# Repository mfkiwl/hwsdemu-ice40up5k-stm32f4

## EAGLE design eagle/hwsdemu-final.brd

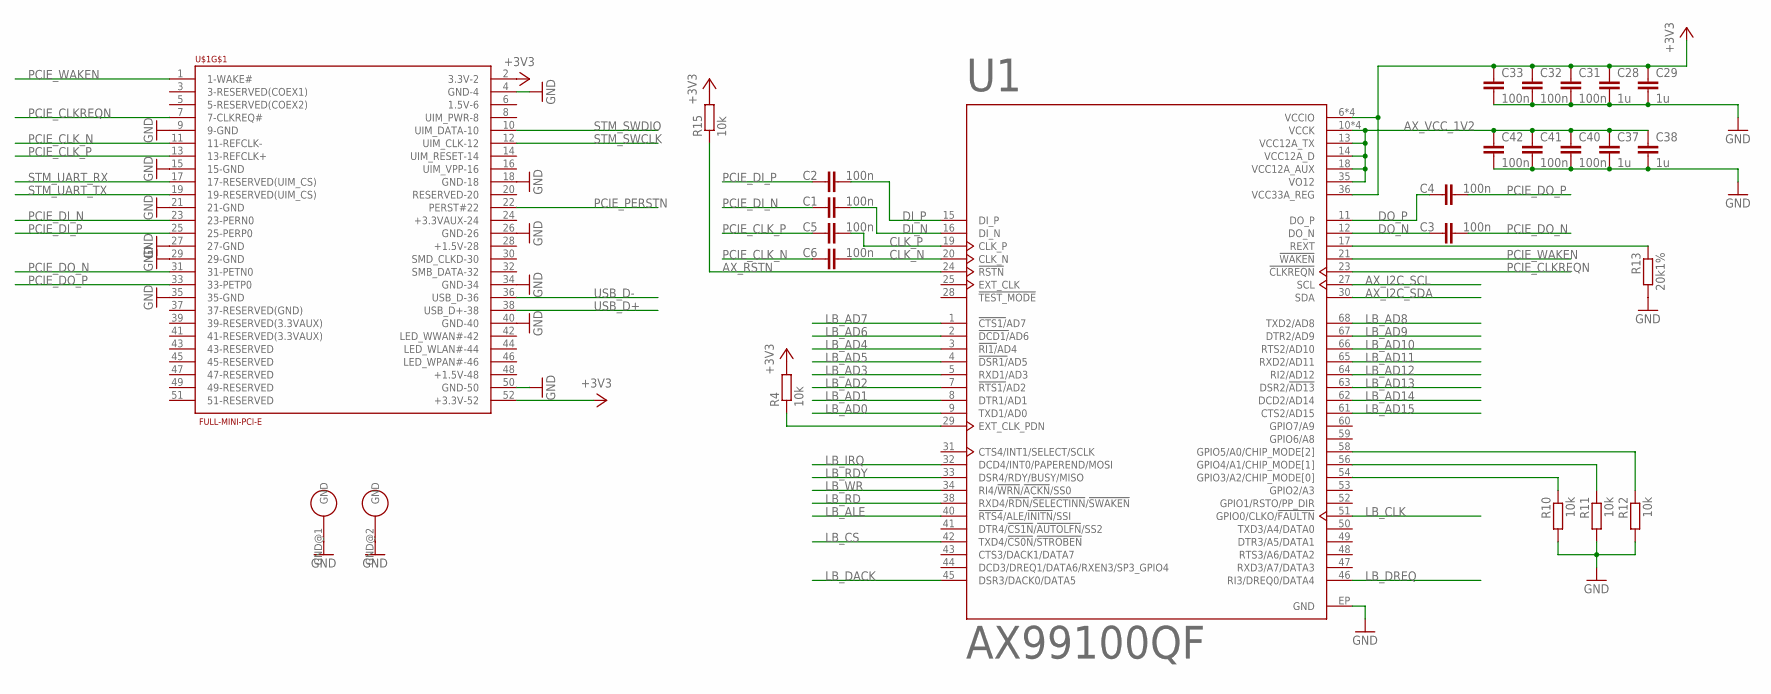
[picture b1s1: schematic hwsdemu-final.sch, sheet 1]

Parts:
C1, C2, C3, C4, C5, C6, C31, C32, C33, C40, C41, C42: 100n; C0402
C28, C29, C37, C38: 1u; C0402
R4, R10, R11, R12, R15: 10k; R0402
R13: 20k1%; R0402
U1: AX99100QF; QFN40P800X800X90-69N
U$1: FULL-MINI-PCI-E

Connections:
+3V3: C28.1, C29.1, C31.1, C32.1, C33.1, R4.2, R15.2, U1.6 (VCCIO), U1.26 (VCCIO), U1.36 (VCC33A_REG), U1.39 (VCCIO), U1.55 (VCCIO), U$1.2 (3.3V-2), U$1.52 (+3.3V-52); also elsewhere on the board
AX_I2C_SCL: U1.27 (SCL); also elsewhere on the board
AX_I2C_SDA: U1.30 (SDA); also elsewhere on the board
AX_RSTN: R15.1, U1.24 (!RSTN); also elsewhere on the board
AX_VCC_1V2: C37.1, C38.1, C40.1, C41.1, C42.1, U1.10 (VCCK), U1.13 (VCC12A_TX), U1.14 (VCC12A_D), U1.18 (VCC12A_AUX), U1.22 (VCCK), U1.35 (VO12), U1.37 (VCCK), U1.57 (VCCK)
CLK_N: C6.2, U1.20 (CLK_N)
CLK_P: C5.2, U1.19 (CLK_P)
DI_N: C1.2, U1.16 (DI_N)
DI_P: C2.2, U1.15 (DI_P)
DO_N: C3.1, U1.12 (DO_N)
DO_P: C4.1, U1.11 (DO_P)
GND: C28.2, C29.2, C31.2, C32.2, C33.2, C37.2, C38.2, C40.2, C41.2, C42.2, R10.2, R11.2, R12.2, R13.2, U1.EP (GND), U$1.4 (GND-4), U$1.9 (9-GND), U$1.15 (15-GND), U$1.18 (GND-18), U$1.21 (21-GND), U$1.26 (GND-26), U$1.27 (27-GND), U$1.29 (29-GND), U$1.34 (GND-34), U$1.35 (35-GND), U$1.40 (GND-40), U$1.50 (GND-50), U$1.GND@1 (GND), U$1.GND@2 (GND); also elsewhere on the board
LB_AD0: U1.9 (TXD1/AD0); also elsewhere on the board
LB_AD1: U1.8 (DTR1/AD1); also elsewhere on the board
LB_AD2: U1.7 (!RTS1/!AD2); also elsewhere on the board
LB_AD3: U1.5 (RXD1/AD3); also elsewhere on the board
LB_AD4: U1.3 (!RI1/!AD4); also elsewhere on the board
LB_AD5: U1.4 (!DSR1/!AD5); also elsewhere on the board
LB_AD6: U1.2 (!DCD1/!AD6); also elsewhere on the board
LB_AD7: U1.1 (!CTS1/!AD7); also elsewhere on the board
LB_AD8: U1.68 (TXD2/AD8); also elsewhere on the board
LB_AD9: U1.67 (DTR2/AD9); also elsewhere on the board
LB_AD10: U1.66 (RTS2/AD10); also elsewhere on the board
LB_AD11: U1.65 (RXD2/AD11); also elsewhere on the board
LB_AD12: U1.64 (RI2/AD12); also elsewhere on the board
LB_AD13: U1.63 (DSR2/!AD13); also elsewhere on the board
LB_AD14: U1.62 (DCD2/AD14); also elsewhere on the board
LB_AD15: U1.61 (CTS2/AD15); also elsewhere on the board
LB_ALE: U1.40 (!RTS4!/ALE/!INITN!/SSI); also elsewhere on the board
LB_CLK: U1.51 (GPIO0/CLKO/!FAULTN); also elsewhere on the board
LB_CS: U1.42 (TXD4/!CS0N!/!STROBEN); also elsewhere on the board
LB_DACK: U1.45 (DSR3/DACK0/DATA5); also elsewhere on the board
LB_DREQ: U1.46 (RI3/DREQ0/DATA4); also elsewhere on the board
LB_IRQ: U1.32 (DCD4/INT0/PAPEREND/MOSI); also elsewhere on the board
LB_RD: U1.38 (RXD4/!RDN!/!SELECTINN!/!SWAKEN); also elsewhere on the board
LB_RDY: U1.33 (DSR4/RDY/BUSY/MISO); also elsewhere on the board
LB_WR: U1.34 (RI4/!WRN!/!ACKN!/SS0); also elsewhere on the board
unnamed: R4.1, U1.29 (EXT_CLK_PDN)
unnamed: R10.1, U1.54 (GPIO3/A2/CHIP_MODE[0])
unnamed: R11.1, U1.56 (GPIO4/A1/CHIP_MODE[1])
unnamed: R12.1, U1.58 (GPIO5/A0/CHIP_MODE[2])
unnamed: R13.1, U1.17 (REXT)
PCIE_CLKREQN: U1.23 (!CLKREQN), U$1.7 (7-CLKREQ#)
PCIE_CLK_N: C6.1, U$1.11 (11-REFCLK-)
PCIE_CLK_P: C5.1, U$1.13 (13-REFCLK+)
PCIE_DI_N: C1.1, U$1.23 (23-PERN0)
PCIE_DI_P: C2.1, U$1.25 (25-PERP0)
PCIE_DO_N: C3.2, U$1.31 (31-PETN0)
PCIE_DO_P: C4.2, U$1.33 (33-PETP0)
PCIE_PERSTN: U$1.22 (PERST#22); also elsewhere on the board
PCIE_WAKEN: U1.21 (!WAKEN), U$1.1 (1-WAKE#)
STM_SWCLK: U$1.12 (UIM_CLK-12); also elsewhere on the board
STM_SWDIO: U$1.10 (UIM_DATA-10); also elsewhere on the board
STM_UART_RX: U$1.17 (17-RESERVED(UIM_CS)); also elsewhere on the board
STM_UART_TX: U$1.19 (19-RESERVED(UIM_CS)); also elsewhere on the board
USB_D+: U$1.38 (USB_D+-38); also elsewhere on the board
USB_D-: U$1.36 (USB_D-36); also elsewhere on the board

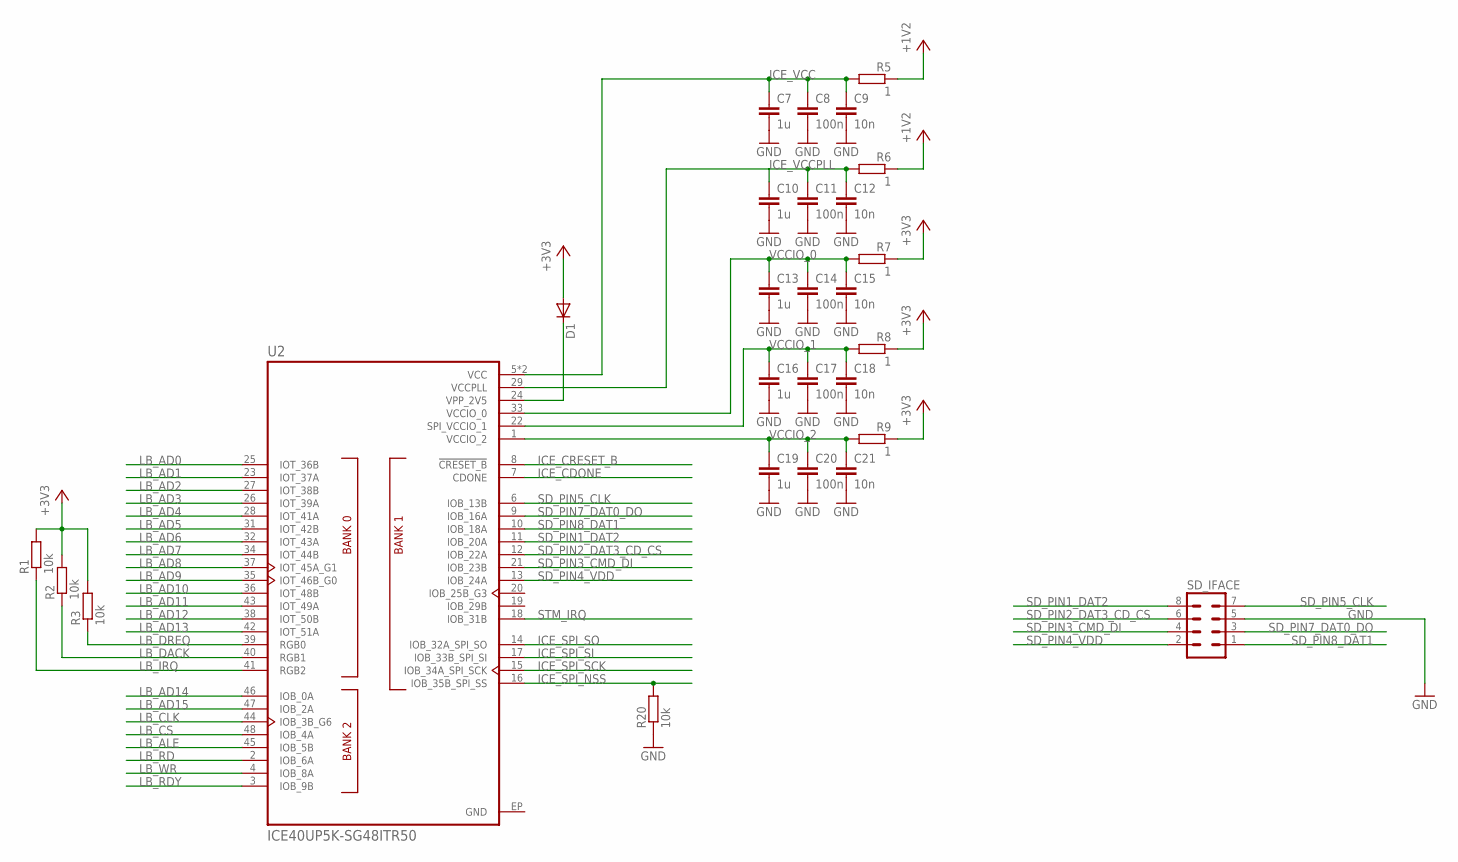
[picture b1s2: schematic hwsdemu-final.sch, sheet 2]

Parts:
C7, C10, C13, C16, C19: 1u; C0402
C8, C11, C14, C17, C20: 100n; C0402
C9, C12, C15, C18, C21: 10n; C0402
D1: DIODE-MICROMELF-W; MICROMELF-W
R1, R2, R3, R20: 10k; R0402
R5, R6, R7, R8, R9: 1; R0402
SD_IFACE: MA04-2
U2: ICE40UP5K-SG48ITR50; QFN50P700X700X100-49N

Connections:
+1V2: R5.1, R6.1; also elsewhere on the board
+3V3: D1.A, R1.2, R2.2, R3.2, R7.1, R8.1, R9.1; also elsewhere on the board
GND: C7.2, C8.2, C9.2, C10.2, C11.2, C12.2, C13.2, C14.2, C15.2, C16.2, C17.2, C18.2, C19.2, C20.2, C21.2, R20.1, SD_IFACE.5, U2.EP (GND); also elsewhere on the board
ICE_CDONE: U2.7 (CDONE); also elsewhere on the board
ICE_CRESET_B: U2.8 (!CRESET_B); also elsewhere on the board
ICE_SPI_NSS: R20.2, U2.16 (IOB_35B_SPI_SS); also elsewhere on the board
ICE_SPI_SCK: U2.15 (IOB_34A_SPI_SCK); also elsewhere on the board
ICE_SPI_SI: U2.17 (IOB_33B_SPI_SI); also elsewhere on the board
ICE_SPI_SO: U2.14 (IOB_32A_SPI_SO); also elsewhere on the board
ICE_VCC: C7.1, C8.1, C9.1, R5.2, U2.5 (VCC), U2.30 (VCC)
ICE_VCCPLL: C10.1, C11.1, C12.1, R6.2, U2.29 (VCCPLL)
LB_AD0: U2.25 (IOT_36B); also elsewhere on the board
LB_AD1: U2.23 (IOT_37A); also elsewhere on the board
LB_AD2: U2.27 (IOT_38B); also elsewhere on the board
LB_AD3: U2.26 (IOT_39A); also elsewhere on the board
LB_AD4: U2.28 (IOT_41A); also elsewhere on the board
LB_AD5: U2.31 (IOT_42B); also elsewhere on the board
LB_AD6: U2.32 (IOT_43A); also elsewhere on the board
LB_AD7: U2.34 (IOT_44B); also elsewhere on the board
LB_AD8: U2.37 (IOT_45A_G1); also elsewhere on the board
LB_AD9: U2.35 (IOT_46B_G0); also elsewhere on the board
LB_AD10: U2.36 (IOT_48B); also elsewhere on the board
LB_AD11: U2.43 (IOT_49A); also elsewhere on the board
LB_AD12: U2.38 (IOT_50B); also elsewhere on the board
LB_AD13: U2.42 (IOT_51A); also elsewhere on the board
LB_AD14: U2.46 (IOB_0A); also elsewhere on the board
LB_AD15: U2.47 (IOB_2A); also elsewhere on the board
LB_ALE: U2.45 (IOB_5B); also elsewhere on the board
LB_CLK: U2.44 (IOB_3B_G6); also elsewhere on the board
LB_CS: U2.48 (IOB_4A); also elsewhere on the board
LB_DACK: R2.1, U2.40 (RGB1); also elsewhere on the board
LB_DREQ: R3.1, U2.39 (RGB0); also elsewhere on the board
LB_IRQ: R1.1, U2.41 (RGB2); also elsewhere on the board
LB_RD: U2.2 (IOB_6A); also elsewhere on the board
LB_RDY: U2.3 (IOB_9B); also elsewhere on the board
LB_WR: U2.4 (IOB_8A); also elsewhere on the board
unnamed: D1.C, U2.24 (VPP_2V5)
SD_PIN1_DAT2: SD_IFACE.8, U2.11 (IOB_20A)
SD_PIN2_DAT3_CD_CS: SD_IFACE.6, U2.12 (IOB_22A)
SD_PIN3_CMD_DI: SD_IFACE.4, U2.21 (IOB_23B)
SD_PIN4_VDD: SD_IFACE.2, U2.13 (IOB_24A)
SD_PIN5_CLK: SD_IFACE.7, U2.6 (IOB_13B)
SD_PIN7_DAT0_DO: SD_IFACE.3, U2.9 (IOB_16A)
SD_PIN8_DAT1: SD_IFACE.1, U2.10 (IOB_18A)
STM_IRQ: U2.18 (IOB_31B); also elsewhere on the board
VCCIO_0: C13.1, C14.1, C15.1, R7.2, U2.33 (VCCIO_0)
VCCIO_1: C16.1, C17.1, C18.1, R8.2, U2.22 (SPI_VCCIO_1)
VCCIO_2: C19.1, C20.1, C21.1, R9.2, U2.1 (VCCIO_2)

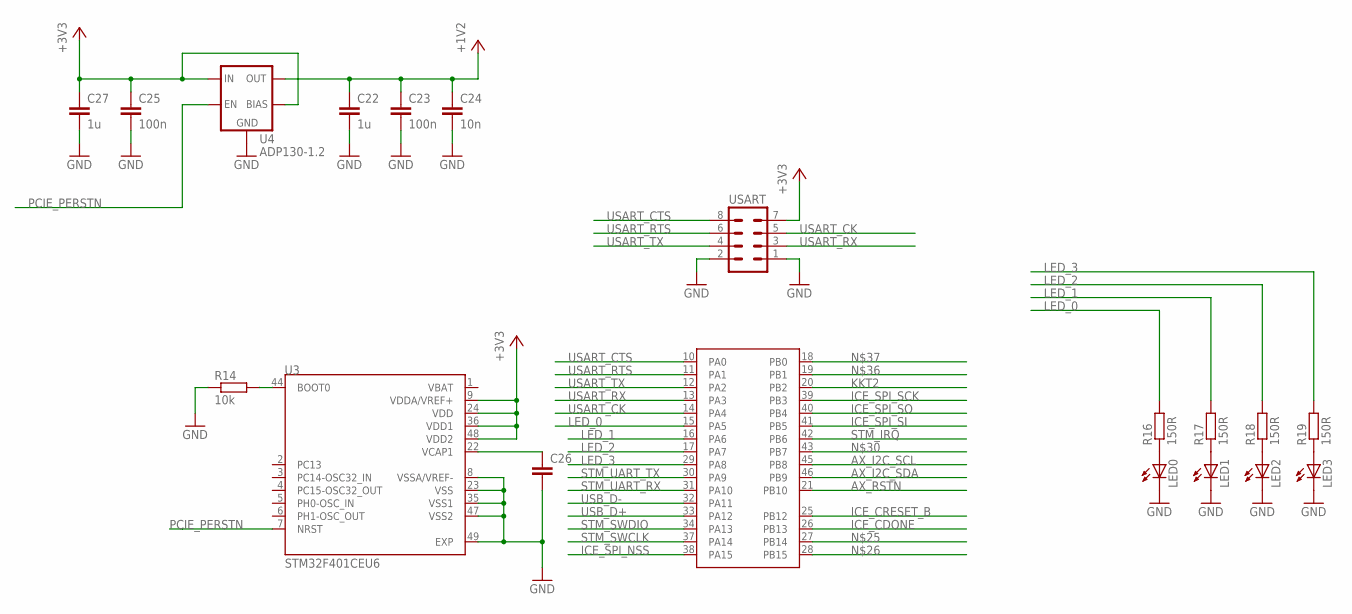
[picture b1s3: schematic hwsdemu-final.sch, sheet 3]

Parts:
C22, C27: 1u; C0402
C23, C25: 100n; C0402
C24: 10n; C0402
C26: C-EUC0402; C0402
LED0, LED1, LED2, LED3: LEDCHIP-LED0603; CHIP-LED0603
R14: 10k; R0402
R16, R17, R18, R19: 150R; R0402
U3: STM32F401CEU6; QFN50P700X700X60-49N
U4: ADP130-1.2; SOT23-5
USART: MA04-2

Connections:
+1V2: C22.1, C23.1, C24.1, U4.5 (OUT); also elsewhere on the board
+3V3: C25.1, C27.1, U3.9 (VDDA/VREF+), U3.24 (VDD), U3.36 (VDD1), U3.48 (VDD2), U4.1 (IN), U4.4 (BIAS), USART.7; also elsewhere on the board
AX_I2C_SCL: U3.45 (PB8); also elsewhere on the board
AX_I2C_SDA: U3.46 (PB9); also elsewhere on the board
AX_RSTN: U3.21 (PB10); also elsewhere on the board
GND: C22.2, C23.2, C24.2, C25.2, C26.2, C27.2, LED0.C, LED1.C, LED2.C, LED3.C, R14.1, U3.8 (VSSA/VREF-), U3.23 (VSS), U3.35 (VSS1), U3.47 (VSS2), U3.49 (EXP), U4.2 (GND), USART.1, USART.2; also elsewhere on the board
ICE_CDONE: U3.26 (PB13); also elsewhere on the board
ICE_CRESET_B: U3.25 (PB12); also elsewhere on the board
ICE_SPI_NSS: U3.38 (PA15); also elsewhere on the board
ICE_SPI_SCK: U3.39 (PB3); also elsewhere on the board
ICE_SPI_SI: U3.41 (PB5); also elsewhere on the board
ICE_SPI_SO: U3.40 (PB4); also elsewhere on the board
KKT2: U3.20 (PB2)
LED_0: R16.2, U3.15 (PA5)
LED_1: R17.2, U3.16 (PA6)
LED_2: R18.2, U3.17 (PA7)
LED_3: R19.2, U3.29 (PA8)
unnamed: R14.2, U3.44 (BOOT0)
unnamed: C26.1, U3.22 (VCAP1)
unnamed: LED0.A, R16.1
unnamed: LED1.A, R17.1
unnamed: LED2.A, R18.1
unnamed: LED3.A, R19.1
PCIE_PERSTN: U3.7 (NRST), U4.3 (EN); also elsewhere on the board
STM_IRQ: U3.42 (PB6); also elsewhere on the board
STM_SWCLK: U3.37 (PA14); also elsewhere on the board
STM_SWDIO: U3.34 (PA13); also elsewhere on the board
STM_UART_RX: U3.31 (PA10); also elsewhere on the board
STM_UART_TX: U3.30 (PA9); also elsewhere on the board
USART_CK: U3.14 (PA4), USART.5
USART_CTS: U3.10 (PA0), USART.8
USART_RTS: U3.11 (PA1), USART.6
USART_RX: U3.13 (PA3), USART.3
USART_TX: U3.12 (PA2), USART.4
USB_D+: U3.33 (PA12); also elsewhere on the board
USB_D-: U3.32 (PA11); also elsewhere on the board
VBAT: U3.1 (VBAT)

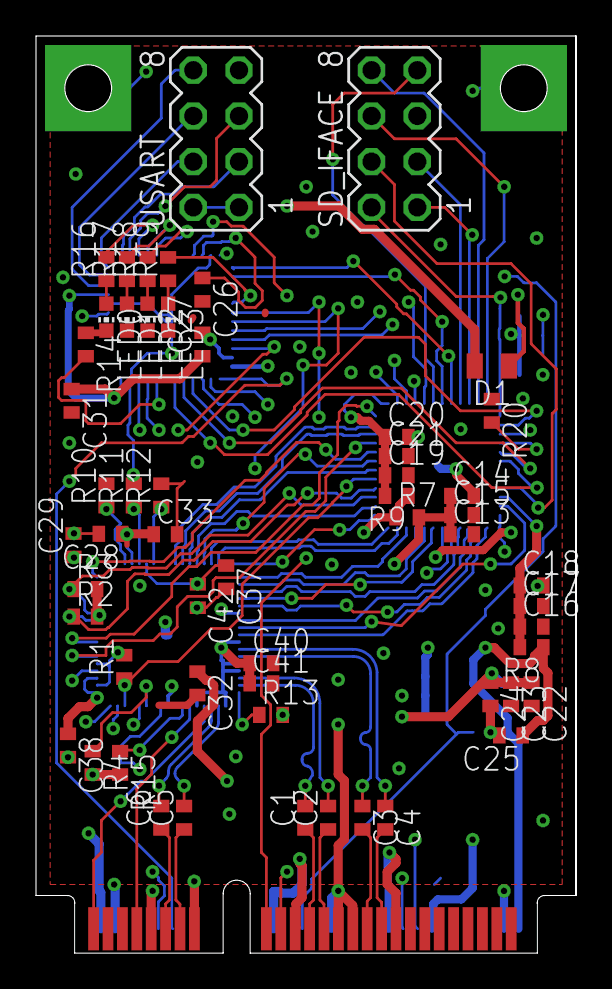
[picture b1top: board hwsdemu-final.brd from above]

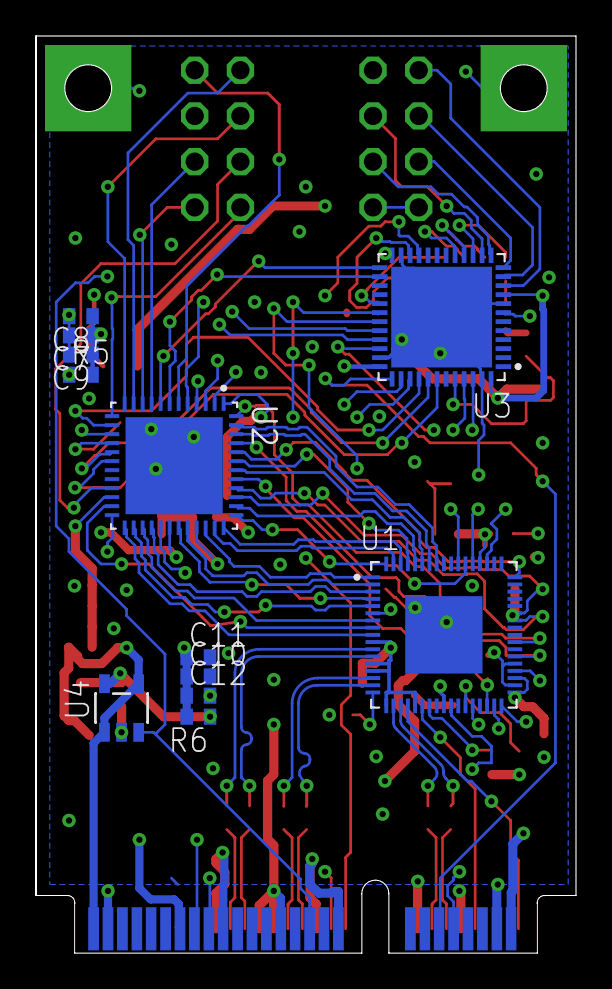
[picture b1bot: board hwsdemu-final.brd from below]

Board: 4 copper layers, 30.0 x 50.9 mm, 69 parts (12 on the bottom side), 93 nets.

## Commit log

2018-05-19 Add Eagle files v1
